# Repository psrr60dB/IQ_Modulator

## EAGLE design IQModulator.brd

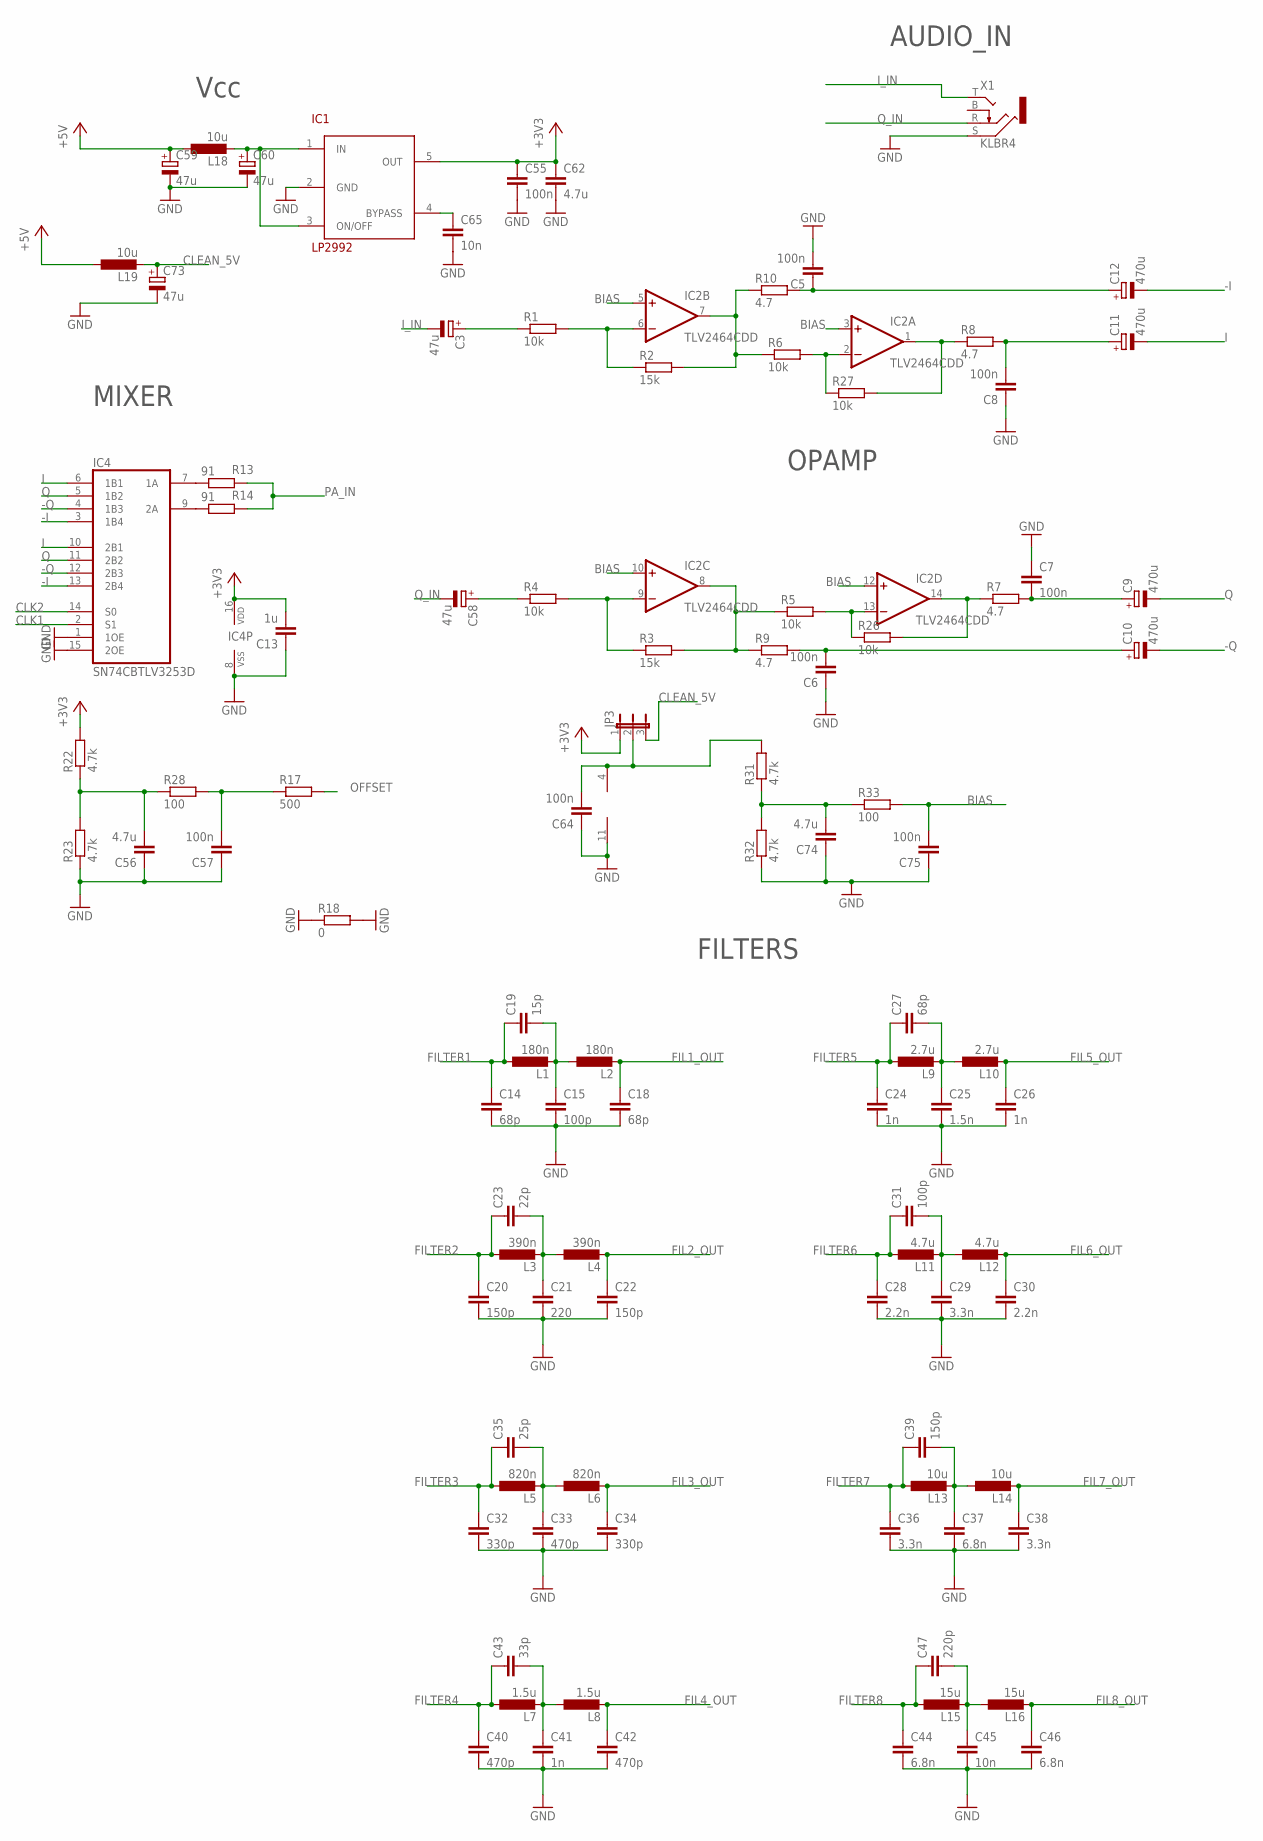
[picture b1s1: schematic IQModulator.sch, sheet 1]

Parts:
C3, C58, C59, C60, C73: 47u; PANASONIC_C
C5, C6, C7, C8, C55, C57, C64, C75: 100n; C0805
C9, C10, C11, C12: 470u; PANASONIC_D
C13: 1u; C0805
C14, C18, C27: 68p; C0805
C15, C31: 100p; C0805
C19: 15p; C0805
C20, C22, C39: 150p; C0805
C21: 220; C0805
C23: 22p; C0805
C24, C26, C41: 1n; C0805
C25: 1.5n; C0805
C28, C30: 2.2n; C0805
C29, C36, C38: 3.3n; C0805
C32, C34: 330p; C0805
C33, C40, C42: 470p; C0805
C35: 25p; C0805
C37, C44, C46: 6.8n; C0805
C43: 33p; C0805
C45, C65: 10n; C0805
C47: 220p; C0805
C56, C62, C74: 4.7u; C0805
IC1: LP2992; SOT-23-5
IC2: TLV2464CDD; SO14
IC4: SN74CBTLV3253D; SO16
JP3: JP2E; JP2
L1, L2: 180n; L0805
L3, L4: 390n; L0805
L5, L6: 820n; L0805
L7, L8: 1.5u; L0805
L9, L10: 2.7u; L0805
L11, L12: 4.7u; L0805
L13, L14: 10u; L0805
L15, L16: 15u; L1008
L18, L19: 10u; L1008
R1, R4, R5, R6, R26, R27: 10k; R0805
R2, R3: 15k; R0805
R7, R8, R9, R10: 4.7; R0805
R13, R14: 91; R0805
R17: 500; R0805
R18: 0; R0805
R22, R23, R31, R32: 4.7k; R0805
R28, R33: 100; R0805
X1: KLBR4

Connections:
+3V3: C13.2, C55.1, C62.1, IC1.5 (OUT), IC4.16 (VDD), JP3.1, R22.2; also elsewhere on the board
+5V: C59.+, L18.P$1 (1), L19.P$1 (1); also elsewhere on the board
-I: C12.-, IC4.3 (1B4), IC4.13 (2B4)
-Q: C10.-, IC4.4 (1B3), IC4.12 (2B3)
BIAS: C75.2, IC2.3 (+IN), IC2.5 (+IN), IC2.10 (+IN), IC2.12 (+IN), R33.2
CLEAN_5V: C73.+, JP3.3, L19.P$2 (2)
CLK1: IC4.2 (S1); also elsewhere on the board
CLK2: IC4.14 (S0); also elsewhere on the board
FIL1_OUT: C18.1, L2.P$2 (2); also elsewhere on the board
FIL2_OUT: C22.1, L4.P$2 (2); also elsewhere on the board
FIL3_OUT: C34.1, L6.P$2 (2); also elsewhere on the board
FIL4_OUT: C42.1, L8.P$2 (2); also elsewhere on the board
FIL5_OUT: C26.1, L10.P$2 (2); also elsewhere on the board
FIL6_OUT: C30.1, L12.P$2 (2); also elsewhere on the board
FIL7_OUT: C38.1, L14.P$2 (2); also elsewhere on the board
FIL8_OUT: C46.1, L16.P$2 (2); also elsewhere on the board
FILTER1: C14.1, C19.1, L1.P$1 (1); also elsewhere on the board
FILTER2: C20.1, C23.1, L3.P$1 (1); also elsewhere on the board
FILTER3: C32.1, C35.1, L5.P$1 (1); also elsewhere on the board
FILTER4: C40.1, C43.1, L7.P$1 (1); also elsewhere on the board
FILTER5: C24.1, C27.1, L9.P$1 (1); also elsewhere on the board
FILTER6: C28.1, C31.1, L11.P$1 (1); also elsewhere on the board
FILTER7: C36.1, C39.1, L13.P$1 (1); also elsewhere on the board
FILTER8: C44.1, C47.1, L15.P$1 (1); also elsewhere on the board
GND: C5.2, C6.1, C7.1, C8.1, C13.1, C14.2, C15.2, C18.2, C20.2, C21.2, C22.2, C24.2, C25.2, C26.2, C28.2, C29.2, C30.2, C32.2, C33.2, C34.2, C36.2, C37.2, C38.2, C40.2, C41.2, C42.2, C44.2, C45.2, C46.2, C55.2, C56.1, C57.1, C59.-, C60.-, C62.2, C64.1, C65.2, C73.-, C74.1, C75.1, IC1.2 (GND), IC2.11 (V-), IC4.1 (1OE), IC4.8 (VSS), IC4.15 (2OE), R18.1, R18.2, R23.1, R32.1, X1.S; also elsewhere on the board
I: C11.-, IC4.6 (1B1), IC4.10 (2B1)
I_IN: C3.-, X1.T
unnamed: C57.2, R17.1, R28.2
unnamed: C3.+, R1.1
unnamed: IC2.6 (-IN), R1.2, R2.1
unnamed: C58.+, R4.1
unnamed: IC2.9 (-IN), R3.1, R4.2
unnamed: IC2.8 (OUT), R3.2, R5.1, R9.1
unnamed: IC2.13 (-IN), R5.2, R26.1
unnamed: IC2.7 (OUT), R2.2, R6.1, R10.1
unnamed: IC2.2 (-IN), R6.2, R27.1
unnamed: IC2.1 (OUT), R8.1, R27.2
unnamed: IC2.14 (OUT), R7.1, R26.2
unnamed: C5.1, C12.+, R10.2
unnamed: C6.2, C10.+, R9.2
unnamed: C7.2, C9.+, R7.2
unnamed: C8.2, C11.+, R8.2
unnamed: IC4.7 (1A), R13.2
unnamed: IC4.9 (2A), R14.2
unnamed: C15.1, C19.2, L1.P$2 (2), L2.P$1 (1)
unnamed: C21.1, C23.2, L3.P$2 (2), L4.P$1 (1)
unnamed: C25.1, C27.2, L9.P$2 (2), L10.P$1 (1)
unnamed: C29.1, C31.2, L11.P$2 (2), L12.P$1 (1)
unnamed: C33.1, C35.2, L5.P$2 (2), L6.P$1 (1)
unnamed: C37.1, C39.2, L13.P$2 (2), L14.P$1 (1)
unnamed: C41.1, C43.2, L7.P$2 (2), L8.P$1 (1)
unnamed: C56.2, R22.1, R23.2, R28.1
unnamed: C45.1, C47.2, L15.P$2 (2), L16.P$1 (1)
unnamed: C65.1, IC1.4 (BYPASS)
unnamed: C74.2, R31.1, R32.2, R33.1
unnamed: C64.2, IC2.4 (V+), JP3.2, R31.2
unnamed: C60.+, IC1.1 (IN), IC1.3 (ON/OFF), L18.P$2 (2)
OFFSET: R17.2; also elsewhere on the board
PA_IN: R13.1, R14.1; also elsewhere on the board
Q: C9.-, IC4.5 (1B2), IC4.11 (2B2)
Q_IN: C58.-, X1.R

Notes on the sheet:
MIXER
OPAMP
Vcc
AUDIO_IN
FILTERS

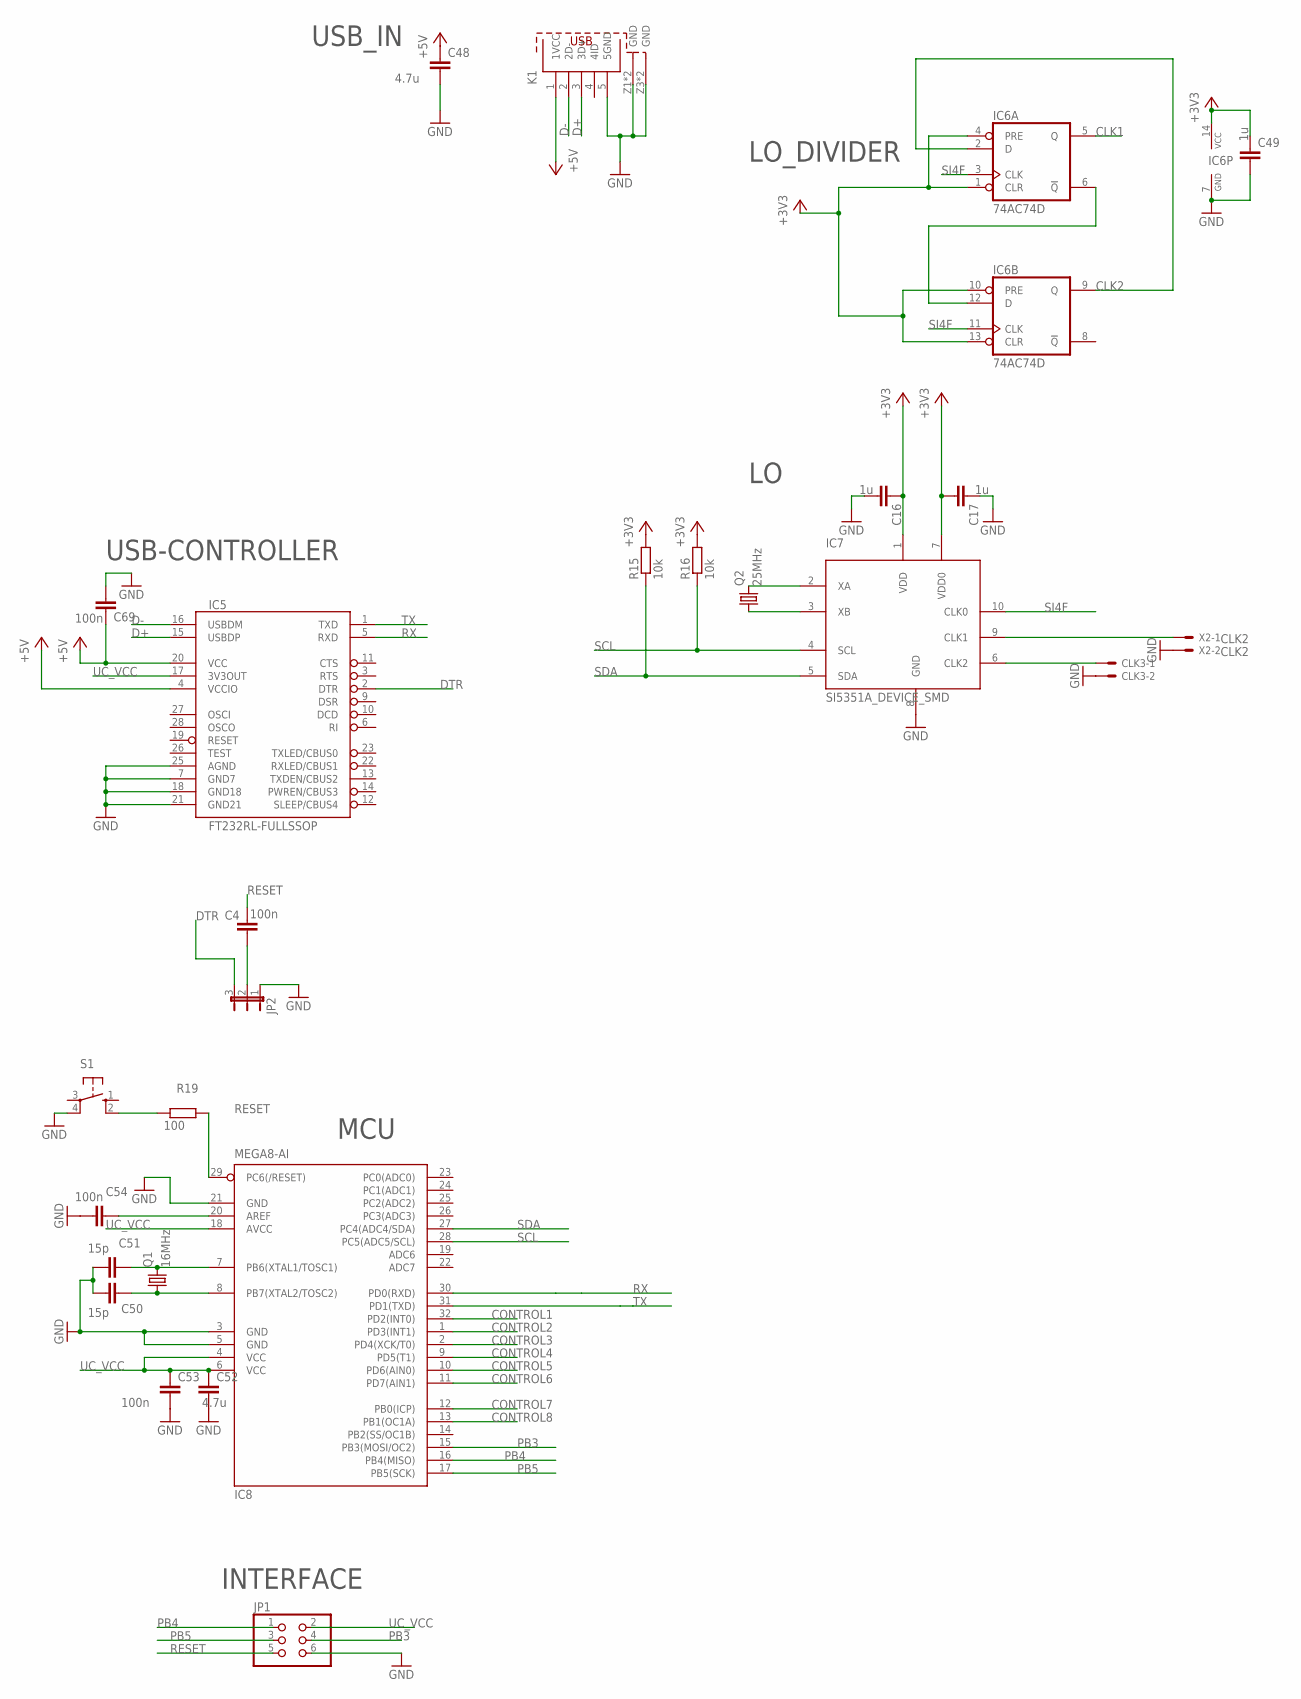
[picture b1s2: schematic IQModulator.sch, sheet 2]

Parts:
C4, C53, C54, C69: 100n; C0805
C16, C17, C49: 1u; C0805
C48, C52: 4.7u; C0805
C50, C51: 15p; C0805
CLK3: KK-156-2
IC5: FT232RL-FULLSSOP; SSOP28DB
IC6: 74AC74D; SO14
IC7: SI5351A_DEVICE_SMD; 10-MSOP
IC8: MEGA8-AI; TQFP32-08
JP1: HEADER-2X3; 2X03_ROUND_70MIL
JP2: JP2E; JP2
K1: 629105150521
Q1: 16MHz; HC49/S
Q2: 25MHz; HC49/S
R15, R16: 10k; R0805
R19: 100; R0805
S1: 10-XX; B3F-10XX
X2: CLK2; KK-156-2

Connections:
+3V3: C16.1, C17.2, C49.1, IC6.1 (CLR), IC6.4 (PRE), IC6.10 (PRE), IC6.13 (CLR), IC6.14 (VCC), IC7.1 (VDD), IC7.7 (VDD0), R15.2, R16.2; also elsewhere on the board
+5V: C48.1, C69.1, IC5.4 (VCCIO), IC5.20 (VCC), K1.1 (1VCC); also elsewhere on the board
CLK1: IC6.5 (Q); also elsewhere on the board
CLK2: IC6.2 (D), IC6.9 (Q); also elsewhere on the board
CONTROL1: IC8.32 (PD2(INT0)); also elsewhere on the board
CONTROL2: IC8.1 (PD3(INT1)); also elsewhere on the board
CONTROL3: IC8.2 (PD4(XCK/T0)); also elsewhere on the board
CONTROL4: IC8.9 (PD5(T1)); also elsewhere on the board
CONTROL5: IC8.10 (PD6(AIN0)); also elsewhere on the board
CONTROL6: IC8.11 (PD7(AIN1)); also elsewhere on the board
CONTROL7: IC8.12 (PB0(ICP)); also elsewhere on the board
CONTROL8: IC8.13 (PB1(OC1A)); also elsewhere on the board
D+: IC5.15 (USBDP), K1.3 (3D+)
D-: IC5.16 (USBDM), K1.2 (2D-)
DTR: IC5.2 (DTR), JP2.3
GND: C16.2, C17.1, C48.2, C49.2, C50.2, C51.2, C52.2, C53.2, C54.2, C69.2, CLK3.2, IC5.7 (GND7), IC5.18 (GND18), IC5.21 (GND21), IC5.25 (AGND), IC6.7 (GND), IC7.8 (GND), IC8.3 (GND), IC8.5 (GND), IC8.21 (GND), JP1.6, JP2.1, K1.5 (5GND), K1.Z1 (GND), K1.Z2 (GND), K1.Z3 (GND), K1.Z4 (GND), S1.4 (P1), X2.2; also elsewhere on the board
unnamed: C51.1, IC8.7 (PB6(XTAL1/TOSC1)), Q1.2
unnamed: IC6.6 (!Q), IC6.12 (D)
unnamed: IC7.3 (XB), Q2.1
unnamed: IC7.2 (XA), Q2.2
unnamed: C4.2, JP2.2
unnamed: R19.1, S1.2 (S1)
unnamed: C50.1, IC8.8 (PB7(XTAL2/TOSC2)), Q1.1
unnamed: C54.1, IC8.20 (AREF)
unnamed: IC7.9 (CLK1), X2.1
unnamed: CLK3.1, IC7.6 (CLK2)
PB3: IC8.15 (PB3(MOSI/OC2)), JP1.4
PB4: IC8.16 (PB4(MISO)), JP1.1
PB5: IC8.17 (PB5(SCK)), JP1.3
RESET: C4.1, IC8.29 (PC6(/RESET)), JP1.5, R19.2
RX: IC5.5 (RXD), IC8.30 (PD0(RXD))
SCL: IC7.4 (SCL), IC8.28 (PC5(ADC5/SCL)), R16.1
SDA: IC7.5 (SDA), IC8.27 (PC4(ADC4/SDA)), R15.1
SI4F: IC6.3 (CLK), IC6.11 (CLK), IC7.10 (CLK0)
TX: IC5.1 (TXD), IC8.31 (PD1(TXD))
UC_VCC: C52.1, C53.1, IC5.17 (3V3OUT), IC8.4 (VCC), IC8.6 (VCC), IC8.18 (AVCC), JP1.2

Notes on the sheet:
USB_IN
LO_DIVIDER
USB-CONTROLLER
MCU
INTERFACE

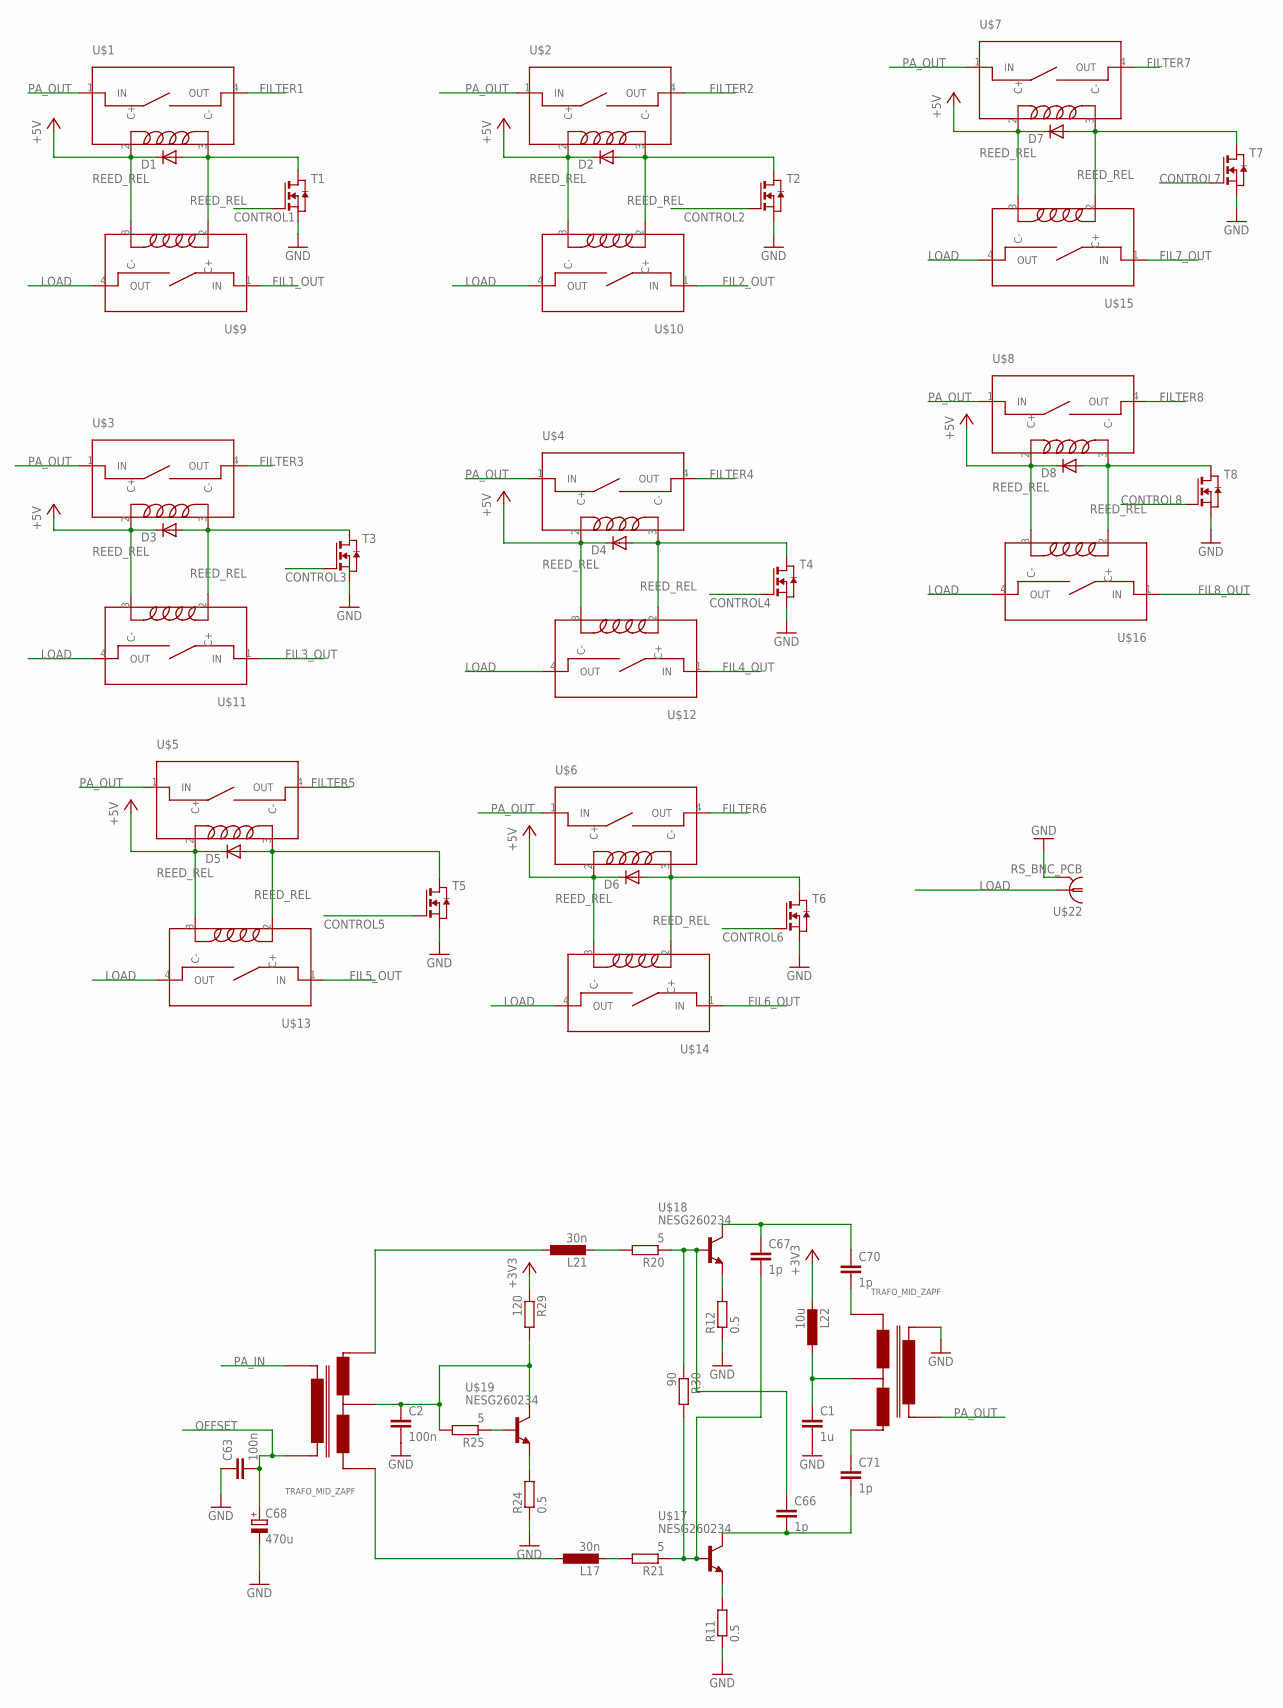
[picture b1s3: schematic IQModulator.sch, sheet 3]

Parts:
C1: 1u; C0805
C2, C63: 100n; C0805
C66, C67, C70, C71: 1p; C0805
C68: 470u; PANASONIC_D
D1, D2, D3, D4, D5, D6, D7, D8: DIODE-DO214AA; DO214AA
L17, L21: 30n; L0805
L22: 10u; L0805
R11, R12, R24: 0.5; R0805
R20, R21, R25: 5; R0805
R29: 120; R0805
R30: 90; R0805
T1, T2, T3, T4, T5, T6, T7, T8: NMOSSOT23; SOT-23
U$1, U$2, U$3, U$4, U$5, U$6, U$7, U$8, U$9, U$10, U$11, U$12, U$13, U$14, U$15, U$16: REED_REL; REED_RELAY
U$17, U$18, U$19: NESG260234; SOT-89
U$20, U$21: TRAFO_MID_ZAPF
U$22: RS_BNC_PCB; COAX-RS

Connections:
+3V3: L22.P$2 (2), R29.1; also elsewhere on the board
+5V: D1.C, D2.C, D3.C, D4.C, D5.C, D6.C, D7.C, D8.C, U$1.2 (C+), U$2.2 (C+), U$3.2 (C+), U$4.2 (C+), U$5.2 (C+), U$6.2 (C+), U$7.2 (C+), U$8.2 (C+), U$9.3 (C-), U$10.3 (C-), U$11.3 (C-), U$12.3 (C-), U$13.3 (C-), U$14.3 (C-), U$15.3 (C-), U$16.3 (C-); also elsewhere on the board
CONTROL1: T1.3 (G); also elsewhere on the board
CONTROL2: T2.3 (G); also elsewhere on the board
CONTROL3: T3.3 (G); also elsewhere on the board
CONTROL4: T4.3 (G); also elsewhere on the board
CONTROL5: T5.3 (G); also elsewhere on the board
CONTROL6: T6.3 (G); also elsewhere on the board
CONTROL7: T7.3 (G); also elsewhere on the board
CONTROL8: T8.3 (G); also elsewhere on the board
FIL1_OUT: U$9.1 (IN); also elsewhere on the board
FIL2_OUT: U$10.1 (IN); also elsewhere on the board
FIL3_OUT: U$11.1 (IN); also elsewhere on the board
FIL4_OUT: U$12.1 (IN); also elsewhere on the board
FIL5_OUT: U$13.1 (IN); also elsewhere on the board
FIL6_OUT: U$14.1 (IN); also elsewhere on the board
FIL7_OUT: U$15.1 (IN); also elsewhere on the board
FIL8_OUT: U$16.1 (IN); also elsewhere on the board
FILTER1: U$1.4 (OUT); also elsewhere on the board
FILTER2: U$2.4 (OUT); also elsewhere on the board
FILTER3: U$3.4 (OUT); also elsewhere on the board
FILTER4: U$4.4 (OUT); also elsewhere on the board
FILTER5: U$5.4 (OUT); also elsewhere on the board
FILTER6: U$6.4 (OUT); also elsewhere on the board
FILTER7: U$7.4 (OUT); also elsewhere on the board
FILTER8: U$8.4 (OUT); also elsewhere on the board
GND: C1.2, C2.2, C63.1, C68.-, R11.1, R12.1, R24.1, T1.2 (S), T2.2 (S), T3.2 (S), T4.2 (S), T5.2 (S), T6.2 (S), T7.2 (S), T8.2 (S), U$21.PRIMARY_BOTTOM (PRIM_BOTTOM), U$22.P$1 (2), U$22.P$2 (2), U$22.P$3 (2), U$22.P$4 (2); also elsewhere on the board
LOAD: U$9.4 (OUT), U$10.4 (OUT), U$11.4 (OUT), U$12.4 (OUT), U$13.4 (OUT), U$14.4 (OUT), U$15.4 (OUT), U$16.4 (OUT), U$22.MID (1)
unnamed: D6.A, T6.1 (D), U$6.3 (C-), U$14.2 (C+)
unnamed: D1.A, T1.1 (D), U$1.3 (C-), U$9.2 (C+)
unnamed: D5.A, T5.1 (D), U$5.3 (C-), U$13.2 (C+)
unnamed: D7.A, T7.1 (D), U$7.3 (C-), U$15.2 (C+)
unnamed: D4.A, T4.1 (D), U$4.3 (C-), U$12.2 (C+)
unnamed: R11.2, U$17.C (E)
unnamed: D3.A, T3.1 (D), U$3.3 (C-), U$11.2 (C+)
unnamed: D8.A, T8.1 (D), U$8.3 (C-), U$16.2 (C+)
unnamed: D2.A, T2.1 (D), U$2.3 (C-), U$10.2 (C+)
unnamed: C71.1, U$21.SECONDARY1 (SEC_TOP)
unnamed: C70.2, U$21.SECONDARY2 (SEC_BOT)
unnamed: R12.2, U$18.C (E)
unnamed: C66.2, C71.2, U$17.E (C)
unnamed: C67.1, C70.1, U$18.E (C)
unnamed: C67.2, R21.1, R30.2, U$17.B
unnamed: C66.1, R20.1, R30.1, U$18.B
unnamed: R24.2, U$19.C (E)
unnamed: R25.1, U$19.B
unnamed: C2.1, R25.2, R29.2, U$19.E (C), U$20.SECONDARY_MID (SEC_MID)
unnamed: L21.P$2 (2), R20.2
unnamed: L17.P$2 (2), R21.2
unnamed: L21.P$1 (1), U$20.SECONDARY1 (SEC_TOP)
unnamed: L17.P$1 (1), U$20.SECONDARY2 (SEC_BOT)
unnamed: C1.1, L22.P$1 (1), U$21.SECONDARY_MID (SEC_MID)
OFFSET: C63.2, C68.+, U$20.PRIMARY_BOTTOM (PRIM_BOTTOM); also elsewhere on the board
PA_IN: U$20.PRIMARY_TOP (PRIM_TOP); also elsewhere on the board
PA_OUT: U$1.1 (IN), U$2.1 (IN), U$3.1 (IN), U$4.1 (IN), U$5.1 (IN), U$6.1 (IN), U$7.1 (IN), U$8.1 (IN), U$21.PRIMARY_TOP (PRIM_TOP)

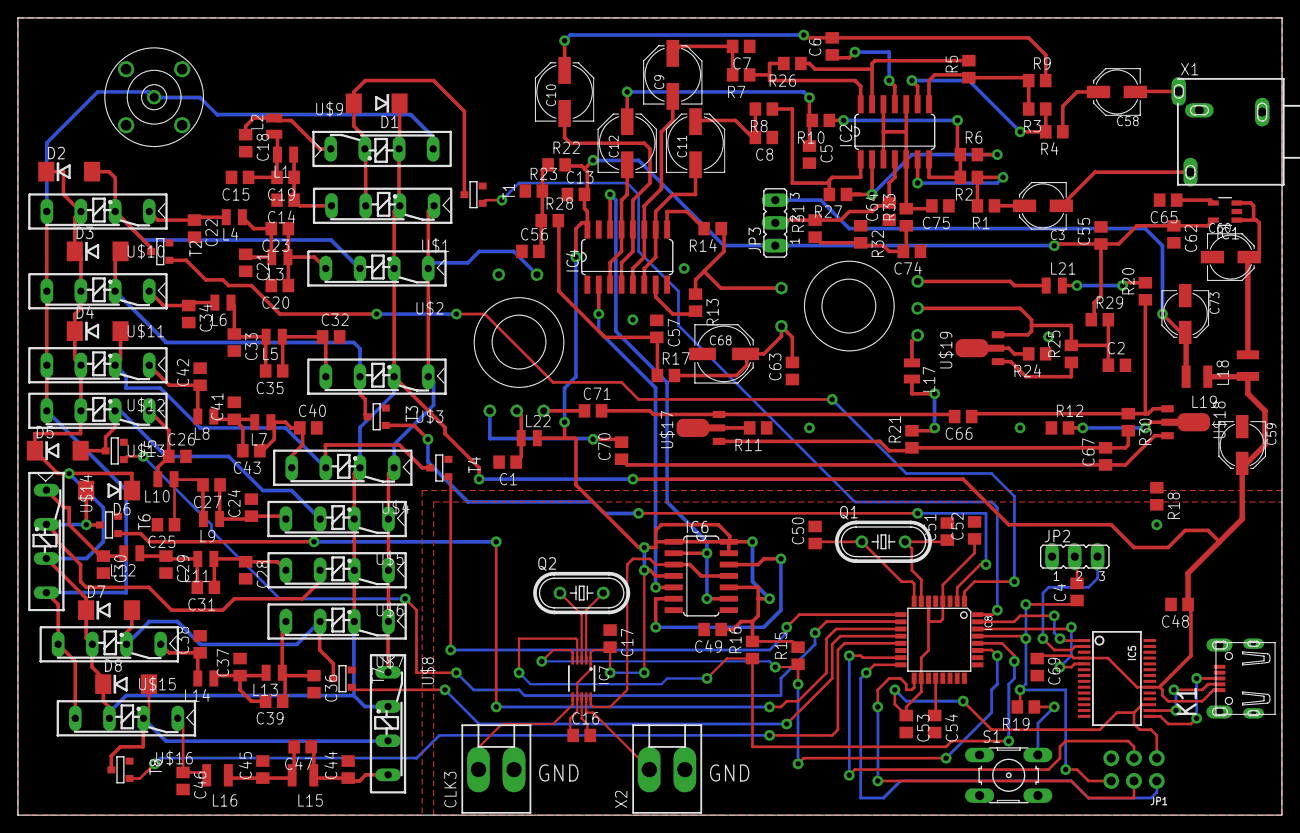
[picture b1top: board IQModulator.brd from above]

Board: 2 copper layers, 140.8 x 88.8 mm, 182 parts (0 on the bottom side), 118 nets.

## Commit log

2016-10-04 Latest Schematic
2016-10-04 test
2016-10-04 Library of Eagle Sch
    Library added
2016-10-04 Filter + Lib
    All Filters designed+ Eagle Lib extended
2016-10-04 Library 04/10 23pm
2016-10-04 Lib Update
    Added 0805 Package for Inductor
2016-10-09 PA+ Relais
    Added last changes in the main schematic
2016-10-09 Added Transistor, BNC, etc...
2016-10-10 Beta V. 0.1
2016-10-15 Started with Layout
2016-10-16 advanced Layout
2016-10-16 updated board
2016-10-17 Board smaller now!
2016-10-17 Close to finish
2016-10-18 Layout done
2016-10-19 error handling
2016-10-25 modded board design
2016-11-02 Ready for gerbhouse

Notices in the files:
parts and their libraries:
microbuilder: This work is placed in the public domain, and may be freely used for commercial and non-commercial work with the following conditions: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
Input-Output_Connectors_rev15d: Copyright: Würth Elektronik
